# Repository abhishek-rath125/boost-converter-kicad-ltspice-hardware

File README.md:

# Non-Isolated Boost DC-DC Converter
### Discrete Hardware Design • KiCad PCB • LTspice Simulation

A high-performance, non-isolated boost (step-up) DC-DC converter designed from discrete power semiconductor and passive components. This repository contains the complete engineering workflow: **theoretical mathematical derivations**, **LTspice SPICE simulation models** (for both CCM and DCM analysis), **KiCad 10 schematic & 2-layer PCB layout**, and **manufacturing Gerbers** for physical lab fabrication.

Developed and validated by **Abhishek Rathour** for **EE306 Tinkering Lab II** in the Department of Electrical & Electronics Engineering at the **National Institute of Technology Goa (NIT Goa)**.

---

## 📸 Hardware Previews

| 3D Isometric View | 3D Top View |
|:---:|:---:|
|  |  |

| 2D PCB Routing & Silkscreen Layout | Schematic PDF Export |
|:---:|:---:|
|  | [📄 Download Schematic PDF](docs/boost_converter_schematic.pdf) |

---

## ⚡ Specifications

| Parameter | Laboratory Target / Measured Value | Notes |
|---|---|---|
| **Converter Topology** | Non-isolated Boost (Step-up), Open-Loop | Discrete power stage |
| **Input Voltage ($V_{in}$)** | **12.0 V DC** | Stable DC bench supply |
| **Output Voltage ($V_{out}$)** | **13.0 V – 24.0 V DC** | Regulated via PWM duty cycle ($D$) |
| **Switching Frequency ($f_{sw}$)** | **20 kHz** ($T_{sw} = 50\,\mu\text{s}$) | Optimized for discrete inductor & switching loss |
| **Measured Efficiency ($\eta$)** | **~91 %** | Measured across nominal operating range |
| **Gate Drive** | External PWM / 555-Timer Generator | $V_{GS} = 0 - 12\,\text{V}$ switching levels |
| **Conduction Modes** | CCM ($R_{load} = 100\,\Omega$) / DCM ($R_{load} = 200\,\Omega$) | Mode verified in simulation & lab hardware |

---

## 🛠️ Key Components & Bill of Materials (BOM)

| Ref Des | Component | Value / Part Number | Description / Package |
|---|---|---|---|
| **$L_1$** | Power Inductor | **$319\,\mu\text{H}$** | Hand-wound toroidal iron-powder core, $R_{ser} \approx 30\,\text{m}\Omega$ |
| **$Q_1$** | Power MOSFET | **IRFZ44N** | N-Channel, $55\,\text{V}$, $49\,\text{A}$, $R_{DS(on)} = 17.5\,\text{m}\Omega$, TO-220 |
| **$D_2$** | Schottky Diode | **MBRF20100SCT** | Dual Schottky barrier, $100\,\text{V}$, $20\,\text{A}$, low $V_F \approx 0.55\,\text{V}$, TO-220F |
| **$C_4, C_6$** | Bulk Capacitors | **$220\,\mu\text{F}$** | Radial electrolytic, low ESR, $50\,\text{V}$ rated |
| **$C_5$** | Decoupling Cap | **$3\,\mu\text{F}$** | High-frequency film/ceramic bypass for output ripple suppression |
| **$R_1$** | Gate Resistor | **$47\,\Omega$** | Damps gate ringing and limits peak gate drive inrush current |
| **$R_2$** | Gate Pull-Down | **$10\,\text{k}\Omega$** | Ensures MOSFET remains off during float/initial power-up |
| **$R_3, R_4$** | Dummy Load | **$200\,\Omega$ each** | Wirewound ceramic power resistors (parallel = $100\,\Omega$) |
| **$J_1, J_2, J_3$** | Terminal Blocks | **2-Pin Connectors** | Screw terminal connections for Input, PWM Gate In, and Load |

---

## 📐 Circuit Theory & Mathematical Derivations

### 1. Steady-State Conversion Ratio (Continuous Conduction Mode)
Applying Faraday's Law of Induction and the inductor volt-second balance over one complete period $T_{sw}$:

$$\int_0^{T_{sw}} v_L(t) \, dt = 0$$

- **During Switch ON interval ($0 \le t \le D T_{sw}$):**  
  The MOSFET conducts. Diode $D_2$ is reverse-biased.
  $$v_L = V_{in}$$

- **During Switch OFF interval ($D T_{sw} \le t \le T_{sw}$):**  
  The MOSFET turns off. The inductor voltage flies up, forward-biasing $D_2$.
  $$v_L = V_{in} - V_{out}$$

Equating the net volt-seconds to zero:
$$V_{in} \cdot D \cdot T_{sw} + (V_{in} - V_{out}) \cdot (1 - D) \cdot T_{sw} = 0$$

$$V_{out} = \frac{V_{in}}{1 - D}$$

### 2. Inductor Current Ripple & Critical Inductance
The peak-to-peak inductor current ripple $\Delta I_L$ is:

$$\Delta I_L = \frac{V_{in} \cdot D}{f_{sw} \cdot L_1}$$

For $V_{in} = 12\,\text{V}$, $D = 0.40$, $f_{sw} = 20\,\text{kHz}$, and $L = 319\,\mu\text{H}$:
$$\Delta I_L = \frac{12 \times 0.40}{20\,000 \times 319 \times 10^{-6}} \approx 0.752\,\text{A}$$

The critical boundary inductance $L_{crit}$ between Continuous Conduction Mode (CCM) and Discontinuous Conduction Mode (DCM):

$$L_{crit} = \frac{R_{load} \cdot D (1 - D)^2}{2 \cdot f_{sw}}$$

- **At $R_{load} = 100\,\Omega$ ($R_3 \parallel R_4$):**  
  $L_{crit} = \frac{100 \times 0.4 \times (0.6)^2}{40\,000} = 360\,\mu\text{H} \approx 319\,\mu\text{H}$  
  The converter operates in continuous conduction with slight ripple margin.
- **At $R_{load} = 200\,\Omega$ (Single $R_3$ active):**  
  $L_{crit} = 720\,\mu\text{H} > 319\,\mu\text{H}$  
  The inductor fully discharges every cycle, shifting the converter into **Discontinuous Conduction Mode (DCM)**.

---

## 🧪 Simulation & Experimental Validation

### Simulation vs. Measurement Agreement
- **LTspice SPICE simulation models** agreed with lab bench measurements within **1 % error margin**.
- Confirmed that conduction mode (CCM vs DCM), not just duty cycle $D$, dictates the conversion ratio of an open-loop boost stage.
- Thermal rating and heat sink sizing of the dummy load resistor and power semiconductor packages are critical factors for sustained operation.

### LTspice Models
The [`ltspice/`](ltspice/) directory includes two validated models:
1. **`boost_converter_open_loop.asc`**: Parameterized duty cycle and stepped load analysis.
2. **`boost_converter_555_pwm.asc`**: Hardware-accurate gate drive generation using an NE555 timer IC.

Refer to [`ltspice/README.md`](ltspice/README.md) for step-by-step instructions and probe setup.

---

## 📁 Repository Layout

```
boost-converter-kicad-ltspice-hardware/
├── README.md                          # Comprehensive project documentation
├── LICENSE                            # MIT License
├── .gitignore                         # KiCad & LTspice gitignore rules
├── hardware/                          # KiCad PCB design files
│   ├── buckboostf.kicad_pro           # KiCad project file
│   ├── buckboostf.kicad_sch           # Schematic sheet with title block
│   ├── buckboostf.kicad_pcb           # 2-layer PCB layout
│   └── gerbers/                       # Fabrication files (RS-274X & Excellon)
│       ├── buckboostf-F_Cu.gbr        # Top copper layer
│       ├── buckboostf-B_Cu.gbr        # Bottom copper layer
│       ├── buckboostf-F_Mask.gbr      # Top solder mask
│       ├── buckboostf-B_Mask.gbr      # Bottom solder mask
│       ├── buckboostf-F_Silkscreen.gbr# Top silkscreen legend
│       ├── buckboostf-Edge_Cuts.gbr   # Board contour outline
│       ├── buckboostf-PTH.drl         # Plated through holes
│       └── buckboostf-job.gbrjob      # KiCad Gerber job description
├── ltspice/                           # SPICE simulation workspace
│   ├── boost_converter_open_loop.asc  # Open-loop boost simulation model
│   ├── boost_converter_555_pwm.asc    # 555-timer PWM driven boost model
│   └── README.md                      # Detailed LTspice simulation guide
└── docs/                              # Visual assets & schematics
    ├── boost_converter_schematic.pdf  # Schematic print (PDF)
    ├── 3d_render_top.png              # Top-down 3D PCB render
    ├── 3d_render_isometric.png        # Isometric 3D PCB render
    └── buckboostf.png                 # PCB layout preview
```

---

## 🚀 Getting Started

### 1. Inspecting & Fabricating the PCB (KiCad)
1. Open [`hardware/buckboostf.kicad_pro`](hardware/buckboostf.kicad_pro) in **KiCad 8.0, 9.0, or 10.0+**.
2. View the schematic in Eeschema and PCB layout in Pcbnew.
3. The manufacturing gerbers are pre-generated in [`hardware/gerbers/`](hardware/gerbers/). You can zip this directory and upload directly to JLCPCB, PCBWay, or OSH Park (standard 2-layer, 1.6 mm FR-4, 1 oz copper).

### 2. Running LTspice Simulations
1. Install [LTspice](https://www.analog.com/en/resources/design-tools-and-calculators/ltspice-simulator.html).
2. Open [`ltspice/boost_converter_open_loop.asc`](ltspice/boost_converter_open_loop.asc).
3. Click **Run** (`Alt + S`) to simulate.
4. Probe `V(vout)` and `I(L1)` to observe steady-state operation and ripple characteristics.

---

## 👨‍💻 Author & Authorizations

**Abhishek Rathour**  
*Undergraduate Student, Electrical and Electronics Engineering (EEE)*  
**National Institute of Technology Goa (NIT Goa)**

- 🌐 **GitHub**: [@abhishek-rath125](https://github.com/abhishek-rath125)
- 💼 **LinkedIn**: [in/abhishek-rathour-94b89434b](https://www.linkedin.com/in/abhishek-rathour-94b89434b/)
- 📧 **Email**: abhishekrathour426@gmail.com

---

## 📄 License
This project is open-source hardware and software licensed under the [MIT License](LICENSE).

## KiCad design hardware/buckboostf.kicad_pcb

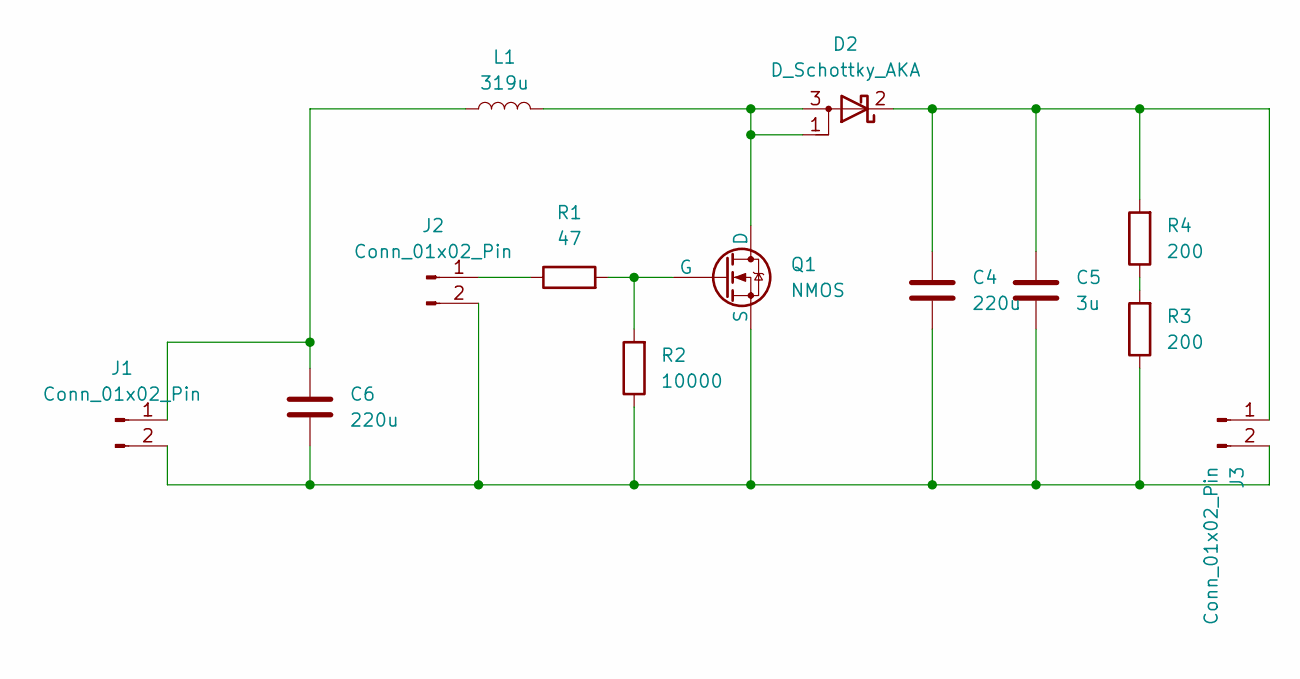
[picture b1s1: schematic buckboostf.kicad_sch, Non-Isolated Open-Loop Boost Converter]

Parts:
C4, C6: 220u; C_Radial_D6.3mm_H11.0mm_P2.50mm
C5: 3u; C_Radial_D4.0mm_H7.0mm_P1.50mm
D2: D_Schottky_AKA; TO-218-3_Vertical
J1, J2, J3: Conn_01x02_Pin; JWT_A3963_1x02_P3.96mm_Vertical
L1: 319u; L_Axial_L17.5mm_D12.0mm_P20.32mm_Horizontal_Vishay_IM-10-46
Q1: NMOS; TO-247-3_Vertical
R1: 47; R_Axial_DIN0207_L6.3mm_D2.5mm_P10.16mm_Horizontal
R2: 10000; R_Axial_DIN0207_L6.3mm_D2.5mm_P10.16mm_Horizontal
R3, R4: 200; R_Axial_DIN0411_L9.9mm_D3.6mm_P15.24mm_Horizontal

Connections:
unnamed: C4.1, C5.1, D2.2 (K), J3.1, R4.2
unnamed: C6.1, J1.1, L1.1
unnamed: C4.2, C5.2, C6.2, J1.2, J2.2, J3.2, Q1.3 (S), R2.1, R3.1
unnamed: J2.1, R1.1
unnamed: D2.1 (A), D2.3 (A), L1.2, Q1.1 (D)
unnamed: Q1.2 (G), R1.2, R2.2
unnamed: R3.2, R4.1

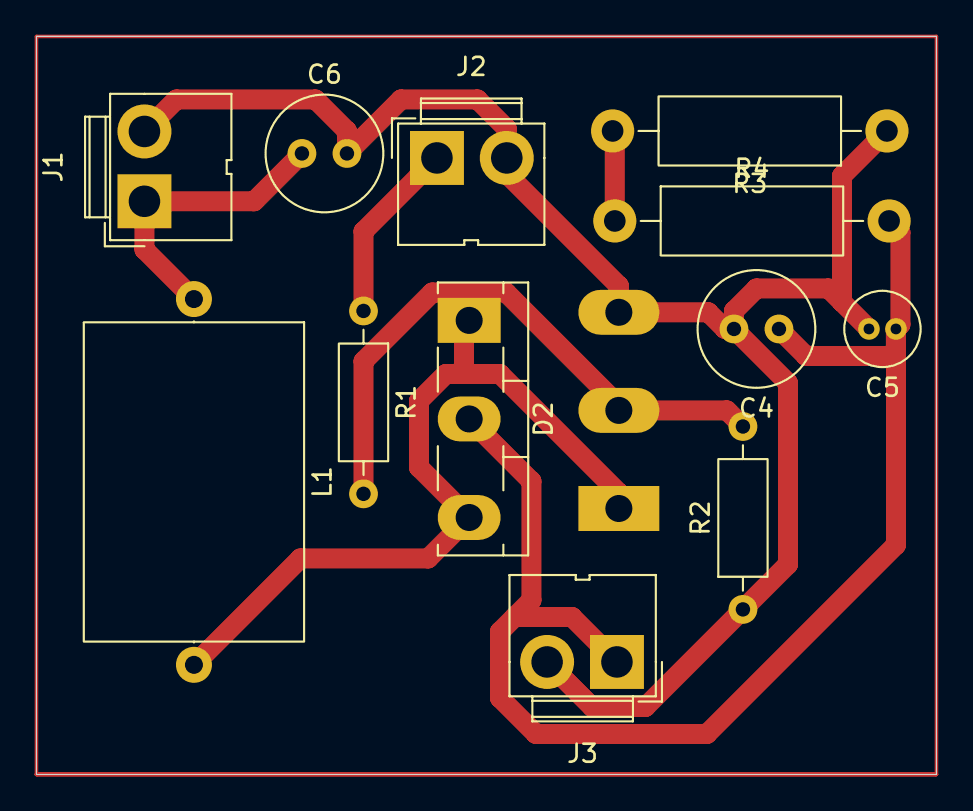
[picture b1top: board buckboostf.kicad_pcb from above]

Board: 2 copper layers, 50.0 x 41.0 mm, 13 parts (1 on the bottom side), 7 nets.
